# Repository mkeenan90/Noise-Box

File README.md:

# Noise-Box
## Summary 
I wanted to create the foundation for a noise machine to fulfill many different purposes around my house. My daughter falls asleep to the sound of lullabies; my wife and I use a fan for noise in our room. I'd like to replicate these noises with my own design.

The desired feature set is too large for the first iteration. These desired features are: bluetooth music streaming, selectable recordings of family members reading bedtime books, a daytime music box (coffee shop noise, meditation tracks, podcast player, etc.), Alexa capable, and whatever else I can think up.

In order to achieve these features, the first design focuses on just playing music from an SD card and a bunch of buttons for user input.

## Design Specification
### Software
Eagle CAD

##Schematic

##Layout

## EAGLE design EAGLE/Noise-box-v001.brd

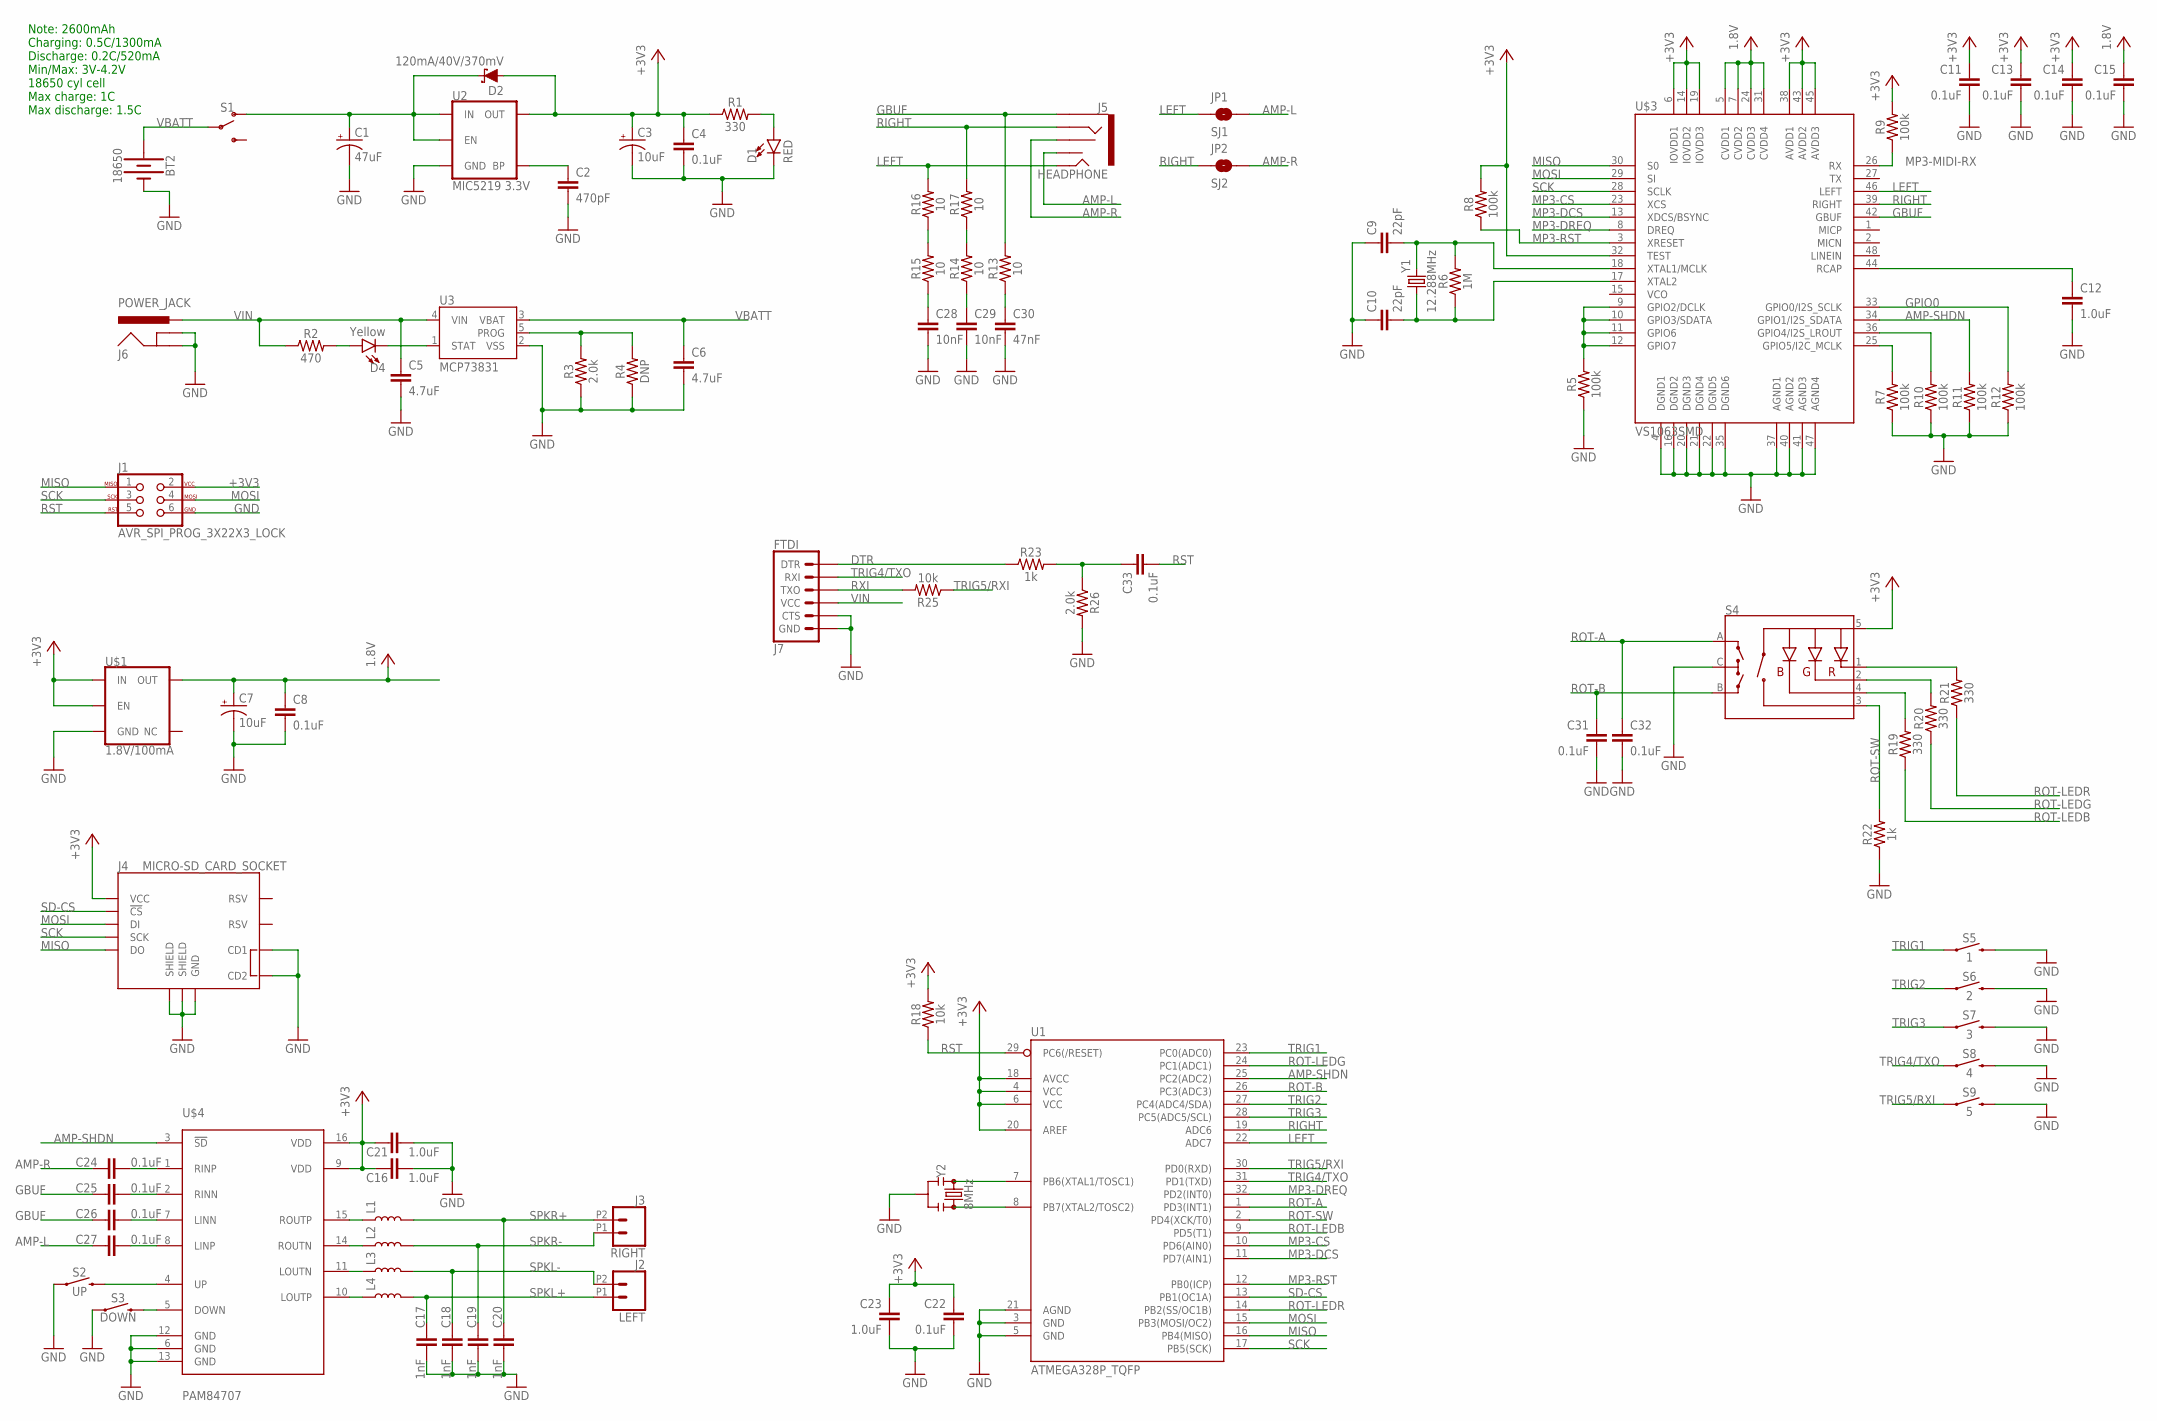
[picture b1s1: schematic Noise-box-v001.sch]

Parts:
BT2: 18650; BATTERY_18650-1043P
C1: 47uF; EIA3528
C2: 470pF; 0603
C3, C7: 10uF; EIA3216
C4, C8, C11, C13, C14, C15, C22, C24, C25, C26, C27, C31, C32, C33: 0.1uF; 0603
C5, C6: 4.7uF; 0603
C9, C10: 22pF; 0603
C12, C16, C21, C23: 1.0uF; 0603
C17, C18, C19, C20: 1nF; 0603
C28, C29: 10nF; 0603
C30: 47nF; 0603
D1: RED; LED-0603
D2: 120mA/40V/370mV; SOD-523
D4: Yellow; LED-0603
J1: AVR_SPI_PROG_3X22X3_LOCK; 2X3_LOCK
J2: LEFT; 1X02_2.54_SCREWTERM
J3: RIGHT; 1X02_2.54_SCREWTERM
J4: MICRO-SD_CARD_SOCKET; MICRO-SD-SOCKET
J5: HEADPHONE; AUDIO-JACK-3.5MM-SMD
J6: POWER_JACK; POWER_JACK_PTH
J7: FTDI; 6_PIN_SERIAL_TARGET_SIDE_W_SILK
JP1: SJ1; SMT-JUMPER_2_NO_SILK
JP2: SJ2; SMT-JUMPER_2_NO_SILK
L1, L2, L3, L4: INDUCTOR-0805-3.3UH; 0805
R1, R19, R20, R21: 330; 0603
R2: 470; 0603
R3, R26: 2.0k; 0603
R4: DNP; 0603
R5, R7, R8, R9, R10, R11, R12: 100k; 0603
R6: 1M; 0603
R13, R14, R15, R16, R17: 10; 0603
R18, R25: 10k; 0603
R22, R23: 1k; 0603
S1: SWITCH-SPDT-SMD-RIGHT-ANGLE; SWITCH_SPST_SMD_A
S2: UP; TACTILE_SWITCH_SMD_4.5MM
S3: DOWN; TACTILE_SWITCH_SMD_4.5MM
S4: ENCODER-RGB-SWITCH; ENCODER_LED_3
S5: 1; TACTILE_SWITCH_SMD_4.5MM
S6: 2; TACTILE_SWITCH_SMD_4.5MM
S7: 3; TACTILE_SWITCH_SMD_4.5MM
S8: 4; TACTILE_SWITCH_SMD_4.5MM
S9: 5; TACTILE_SWITCH_SMD_4.5MM
U1: ATMEGA328P_TQFP; TQFP32-08
U2: MIC5219 3.3V; SOT23-5
U3: MCP73831; SOT23-5
U$1: 1.8V/100mA; SC70
U$3: VS1063SMD; LQFP-48
U$4: PAM84707; SO16
Y1: 12.288MHz; CRYSTAL-SMD-5X3.2-4PAD
Y2: 8MHz; RESONATOR-SMD-3.2X1.3

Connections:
+3V3: C3.+, C4.1, C11.1, C13.1, C14.1, C16.1, C21.1, C22.1, C23.1, D2.A, J1.2, J4.VCC, R1.1, R8.2, R9.2, R18.2, S4.5 (+), U1.4 (VCC), U1.6 (VCC), U1.18 (AVCC), U1.20 (AREF), U2.5 (OUT), U$1.1 (IN), U$1.3 (EN), U$3.6 (IOVDD1), U$3.14 (IOVDD2), U$3.19 (IOVDD3), U$3.32 (TEST), U$3.38 (AVDD1), U$3.43 (AVDD2), U$3.45 (AVDD3), U$4.9 (VDD), U$4.16 (VDD)
AMP-L: C27.1, J5.TSH, JP1.2
AMP-R: C24.1, J5.RSH, JP2.2
AMP-SHDN: R11.2, U1.25 (PC2(ADC2)), U$3.34 (GPIO1/I2S_SDATA), U$4.3 (!SD)
DTR: J7.P$1 (DTR), R23.1
GBUF: C25.1, C26.1, J5.SLEEVE, R13.2, U$3.42 (GBUF)
GND: BT2.GND@1 (-), C1.C (-), C2.2, C3.-, C4.2, C5.2, C6.2, C7.-, C8.2, C9.1, C10.1, C11.2, C12.2, C13.2, C14.2, C15.2, C16.2, C17.2, C18.2, C19.2, C20.2, C21.2, C22.2, C23.2, C28.2, C29.2, C30.2, C31.2, C32.2, D1.C, J1.6, J4.CD1, J4.CD2, J4.GND, J4.GND1 (SHIELD), J4.GND3 (SHIELD), J6.GND, J6.GNDBREAK, J7.P$5 (CTS), J7.P$6 (GND), R3.1, R4.1, R5.1, R7.1, R10.1, R11.1, R12.1, R22.1, R26.2, S2.2 (1), S2.3 (1), S3.2 (1), S3.3 (1), S4.C, S5.1 (2), S5.4 (2), S6.1 (2), S6.4 (2), S7.1 (2), S7.4 (2), S8.1 (2), S8.4 (2), S9.1 (2), S9.4 (2), U1.3 (GND), U1.5 (GND), U1.21 (AGND), U2.2 (GND), U3.2 (VSS), U$1.2 (GND), U$3.4 (DGND1), U$3.16 (DGND2), U$3.20 (DGND3), U$3.21 (DGND4), U$3.22 (DGND5), U$3.35 (DGND6), U$3.37 (AGND1), U$3.40 (AGND2), U$3.41 (AGND3), U$3.47 (AGND4), U$4.6 (GND), U$4.12 (GND), U$4.13 (GND), Y2.2
GPIO0: R12.2, U$3.33 (GPIO0/I2S_SCLK)
LEFT: J5.TIP, JP1.1, R16.2, U1.22 (ADC7), U$3.46 (LEFT)
MISO: J1.1, J4.DO, U1.16 (PB4(MISO)), U$3.30 (S0)
MOSI: J1.4, J4.DI, U1.15 (PB3(MOSI/OC2)), U$3.29 (SI)
MP3-CS: U1.10 (PD6(AIN0)), U$3.23 (XCS)
MP3-DCS: U1.11 (PD7(AIN1)), U$3.13 (XDCS/BSYNC)
MP3-DREQ: U1.32 (PD2(INT0)), U$3.8 (DREQ)
MP3-MIDI-RX: R9.1, U$3.26 (RX)
MP3-RST: R8.1, U1.12 (PB0(ICP)), U$3.3 (XRESET)
unnamed: D4.A, R2.2
unnamed: C2.1, U2.4 (BP)
unnamed: D1.A, R1.2
unnamed: R3.2, R4.2, U3.5 (PROG)
unnamed: U1.7 (PB6(XTAL1/TOSC1)), Y2.1
unnamed: R5.2, U$3.9 (GPIO2/DCLK), U$3.10 (GPIO3/SDATA), U$3.11 (GPIO6), U$3.12 (GPIO7)
unnamed: D4.C, U3.1 (STAT)
unnamed: U1.8 (PB7(XTAL2/TOSC2)), Y2.3
unnamed: L1.1, U$4.15 (ROUTP)
unnamed: L2.1, U$4.14 (ROUTN)
unnamed: L3.1, U$4.11 (LOUTN)
unnamed: L4.1, U$4.10 (LOUTP)
unnamed: C28.1, R15.1
unnamed: R7.2, U$3.25 (GPIO5/I2C_MCLK)
unnamed: R10.2, U$3.36 (GPIO4/I2S_LROUT)
unnamed: C29.1, R14.1
unnamed: C9.2, R6.2, U$3.18 (XTAL1/MCLK), Y1.3 (2)
unnamed: C10.2, R6.1, U$3.17 (XTAL2), Y1.1
unnamed: C30.1, R13.1
unnamed: R15.2, R16.1
unnamed: C12.1, U$3.44 (RCAP)
unnamed: R14.2, R17.1
unnamed: C24.2, U$4.1 (RINP)
unnamed: C33.1, R23.2, R26.1
unnamed: R19.2, S4.4 (-B)
unnamed: R20.2, S4.2 (-G)
unnamed: R21.2, S4.1 (-R)
unnamed: C25.2, U$4.2 (RINN)
unnamed: C26.2, U$4.7 (LINN)
unnamed: C27.2, U$4.8 (LINP)
unnamed: S3.1 (2), S3.4 (2), U$4.5 (DOWN)
unnamed: S2.1 (2), S2.4 (2), U$4.4 (UP)
unnamed: C1.A (+), D2.C, S1.1 (O), U2.1 (IN), U2.3 (EN)
RIGHT: J5.RING, JP2.1, R17.2, U1.19 (ADC6), U$3.39 (RIGHT)
ROT-A: C32.1, S4.A, U1.1 (PD3(INT1))
ROT-B: C31.1, S4.B, U1.26 (PC3(ADC3))
ROT-LEDB: R19.1, U1.9 (PD5(T1))
ROT-LEDG: R20.1, U1.24 (PC1(ADC1))
ROT-LEDR: R21.1, U1.14 (PB2(SS/OC1B))
ROT-SW: R22.2, S4.3 (SW), U1.2 (PD4(XCK/T0))
RST: C33.2, J1.5, R18.1, U1.29 (PC6(/RESET))
RXI: J7.P$2 (TXO), R25.2
SCK: J1.3, J4.SCLK (SCK), U1.17 (PB5(SCK)), U$3.28 (SCLK)
SD-CS: J4.CS (!CS), U1.13 (PB1(OC1A))
SPKL+: C17.1, J2.P1 (1), L4.2
SPKL-: C18.1, J2.P2 (2), L3.2
SPKR+: C20.1, J3.P2 (2), L1.2
SPKR-: C19.1, J3.P1 (1), L2.2
TRIG1: S5.2 (1), S5.3 (1), U1.23 (PC0(ADC0))
TRIG2: S6.2 (1), S6.3 (1), U1.27 (PC4(ADC4/SDA))
TRIG3: S7.2 (1), S7.3 (1), U1.28 (PC5(ADC5/SCL))
TRIG4/TXO: J7.P$3 (RXI), S8.2 (1), S8.3 (1), U1.31 (PD1(TXD))
TRIG5/RXI: R25.1, S9.2 (1), S9.3 (1), U1.30 (PD0(RXD))
VBATT: BT2.PWR@1 (+), C6.1, S1.2, U3.3 (VBAT)
VCC: C7.+, C8.1, C15.1, U$1.5 (OUT), U$3.5 (CVDD1), U$3.7 (CVDD2), U$3.24 (CVDD3), U$3.31 (CVDD4)
VIN: C5.1, J6.PWR, J7.P$4 (VCC), R2.1, U3.4 (VIN)

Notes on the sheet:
Note: 2600mAh Charging: 0.5C/1300mA Discharge: 0.2C/520mA Min/Max: 3V-4.2V 18650 cyl cell Max charge: 1C Max discharge: 1.5C

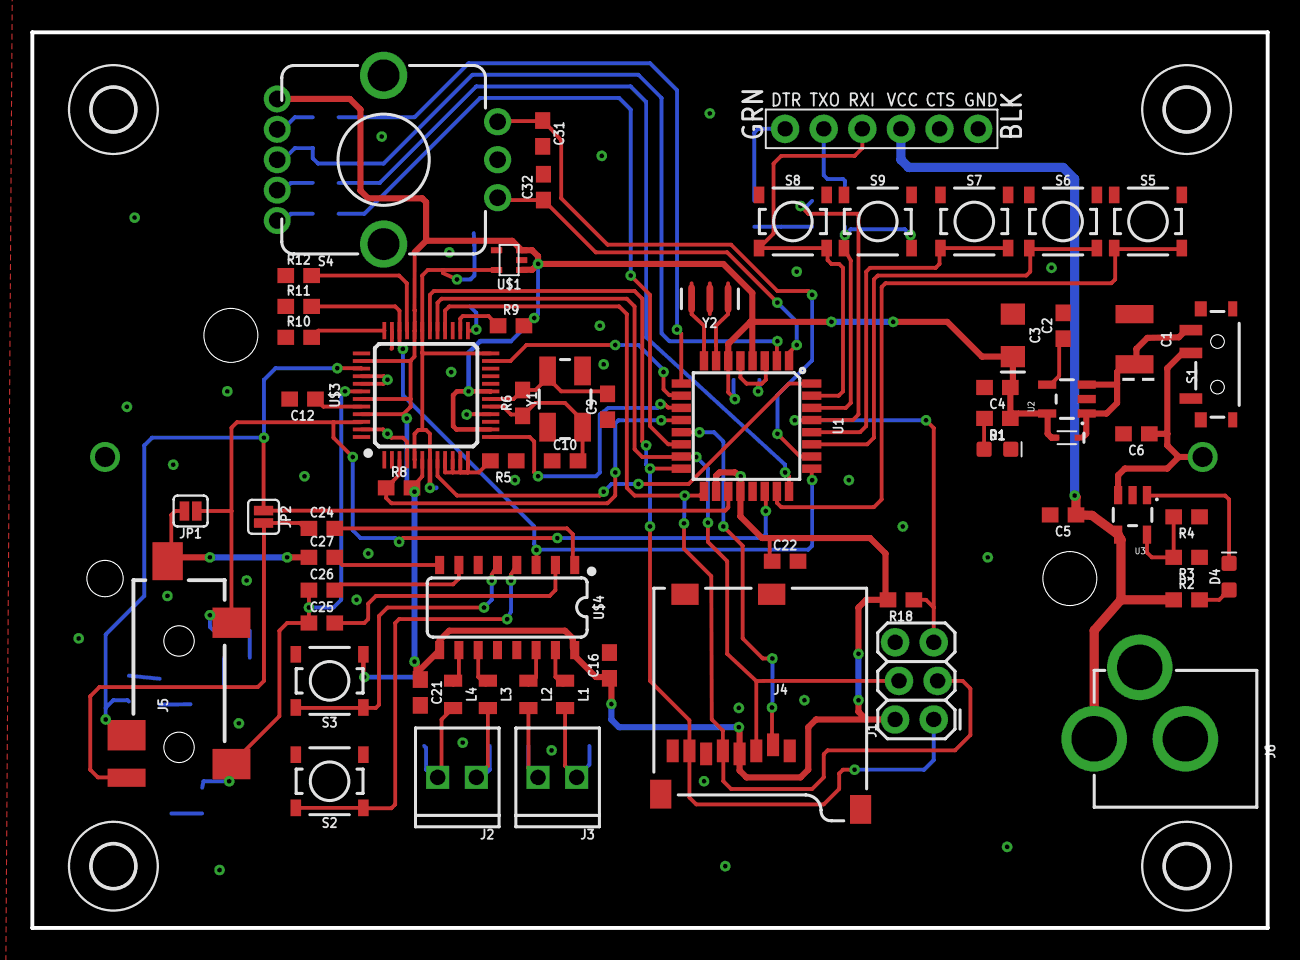
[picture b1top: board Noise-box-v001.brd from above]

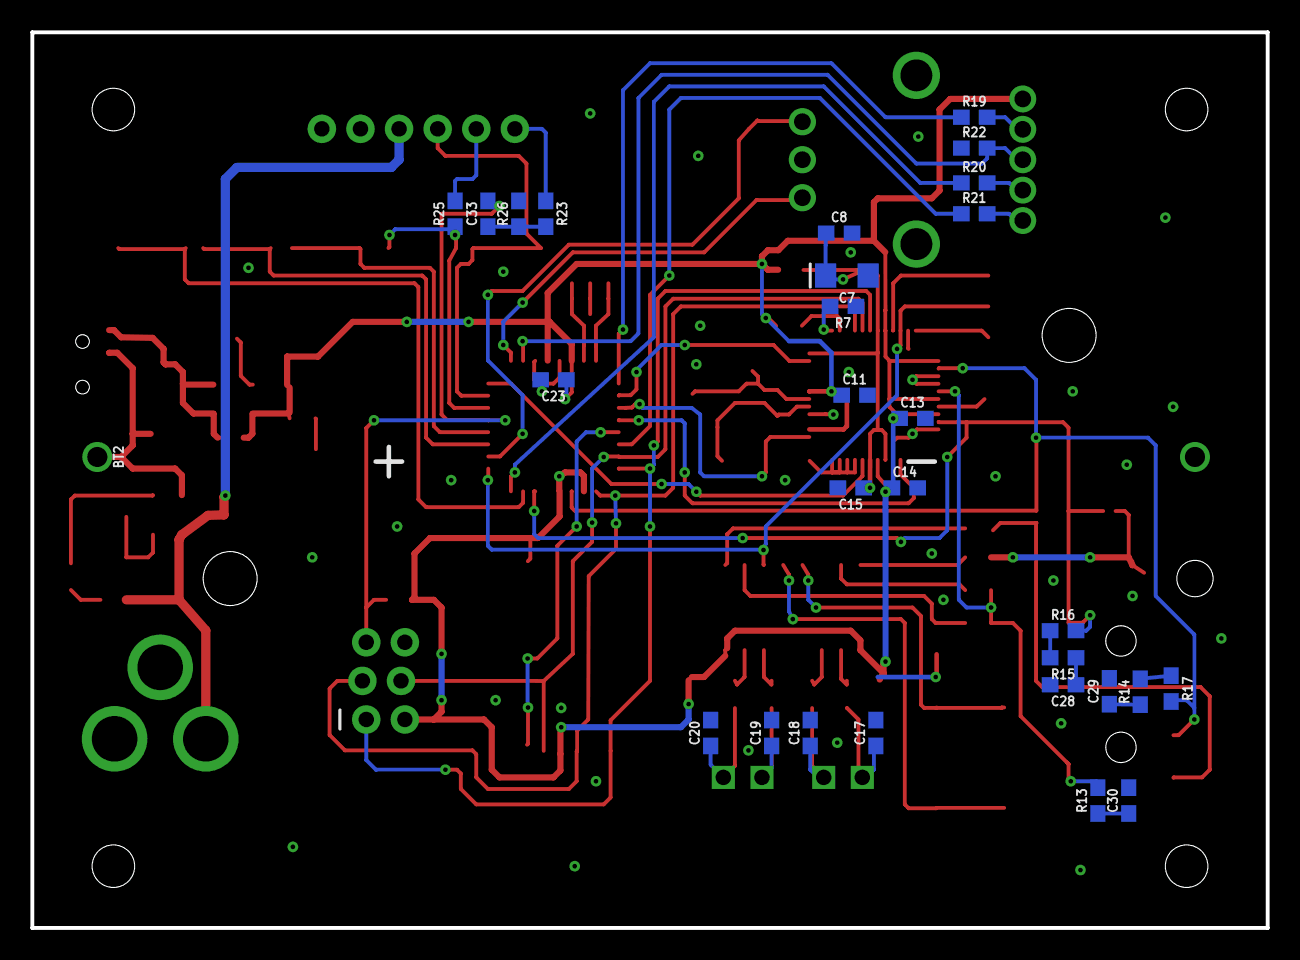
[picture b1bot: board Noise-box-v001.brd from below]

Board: 2 copper layers, 81.3 x 58.9 mm, 96 parts (29 on the bottom side), 72 nets.

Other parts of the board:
U$2, U$5, U$6, U$7: 2,8

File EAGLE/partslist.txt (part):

Partlist

Exported from Noise-box-v001.brd at 3/4/2017 12:36:09 AM

EAGLE Version 6.6.0 Copyright (c) 1988-2014 CadSoft

Assembly variant: 

Part     Value                    Package                         Library                     Position (mm)         Orientation

BT2      18650                    BATTERY_18650-1043P             MAK                         (38.1 27.94)          MR0
C1       47uF                     EIA3528                         SparkFun-Capacitors         (69.723 35.687)       R270
C2       470pF                    0603                            SparkFun-Capacitors         (65.024 36.576)       R90
C3       10uF                     EIA3216                         SparkFun-Capacitors         (61.722 35.941)       R270
C4       0.1uF                    0603                            SparkFun-Capacitors         (60.706 32.512)       R180
C5       4.7uF                    0603                            SparkFun-Capacitors         (65.024 24.13)        R180
C6       4.7uF                    0603                            SparkFun-Capacitors         (69.85 29.464)        R180
C7       10uF                     EIA3216                         SparkFun-Capacitors         (24.892 39.878)       MR180
C8       0.1uF                    0603                            SparkFun-Capacitors         (25.4 42.672)         MR0
C9       22pF                     0603                            SparkFun-Capacitors         (35.052 31.242)       R90
C10      22pF                     0603                            SparkFun-Capacitors         (32.258 27.686)       R0
C11      0.1uF                    0603                            SparkFun-Capacitors         (24.384 32.004)       MR0
C12      1.0uF                    0603                            SparkFun-Capacitors         (14.986 31.75)        R180
C13      0.1uF                    0603                            SparkFun-Capacitors         (20.574 30.48)        MR0
C14      0.1uF                    0603                            SparkFun-Capacitors         (21.082 25.908)       MR0
C15      0.1uF                    0603                            SparkFun-Capacitors         (24.638 25.908)       MR180
C16      1.0uF                    0603                            SparkFun-Capacitors         (35.179 14.224)       R90
C17      1nF                      0603                            SparkFun-Capacitors         (22.987 9.779)        MR90
C18      1nF                      0603                            SparkFun-Capacitors         (27.305 9.779)        MR90
C19      1nF                      0603                            SparkFun-Capacitors         (29.845 9.779)        MR90
C20      1nF                      0603                            SparkFun-Capacitors         (33.8582 9.779)       MR90
C21      1.0uF                    0603                            SparkFun-Capacitors         (22.733 12.446)       R270
C22      0.1uF                    0603                            SparkFun-Capacitors         (46.736 21.082)       R0
C23      1.0uF                    0603                            SparkFun-Capacitors         (44.196 33.02)        MR180
C24      0.1uF                    0603                            SparkFun-Capacitors         (16.256 23.241)       R0
C25      0.1uF                    0603                            SparkFun-Capacitors         (16.256 17.018)       R0
C26      0.1uF                    0603                            SparkFun-Capacitors         (16.256 19.177)       R0
C27      0.1uF                    0603                            SparkFun-Capacitors         (16.256 21.336)       R0
C28      10nF                     0603                            SparkFun-Capacitors         (10.668 12.954)       MR180
C29      10nF                     0603                            SparkFun-Capacitors         (7.62 12.5222)        MR90
C30      47nF                     0603                            SparkFun-Capacitors         (6.35 5.334)          MR90
C31      0.1uF                    0603                            SparkFun-Capacitors         (30.7848 49.2252)     R270
C32      0.1uF                    0603                            SparkFun-Capacitors         (30.8356 45.6946)     R90
C33      0.1uF                    0603                            SparkFun-Capacitors         (48.514 43.942)       MR90
D1       RED                      LED-0603                        SparkFun-LED                (60.706 28.448)       R0
D2       120mA/40V/370mV          SOD-523                         SparkFun-DiscreteSemi       (65.278 29.21)        R0
D4       Yellow                   LED-0603                        SparkFun-LED                (75.946 20.066)       R90
J1       AVR_SPI_PROG_3X22X3_LOCK 2X3_LOCK                        SparkFun-Connectors         (56.642 10.668)       R90
J2       LEFT                     1X02_2.54_SCREWTERM             SparkFun-Connectors         (26.416 6.858)        R180
J3       RIGHT                    1X02_2.54_SCREWTERM             SparkFun-Connectors         (33.02 6.858)         R180
J4       MICRO-SD_CARD_SOCKET     MICRO-SD-SOCKET                 SparkFun-Connectors         (38.1 19.304)         R180
J5       HEADPHONE                AUDIO-JACK-3.5MM-SMD            SparkFun-Connectors         (6.858 5.334)         R90
J6       POWER_JACK               POWER_JACK_PTH                  SparkFun-Connectors         (80.772 9.398)        R90
J7       FTDI                     6_PIN_SERIAL_TARGET_SIDE_W_SILK SparkFun-Connectors         (53.086 49.53)        R0
JP1      SJ1                      SMT-JUMPER_2_NO_SILK            SparkFun-Jumpers            (7.62 24.384)         R180
JP2      SJ2                      SMT-JUMPER_2_NO_SILK            SparkFun-Jumpers            (12.4206 24.003)      R270
L1                                0805                            SparkFun-Coils              (32.258 12.319)       R270
L2                                0805                            SparkFun-Coils              (29.845 12.319)       R270
L3                                0805                            SparkFun-Coils              (27.178 12.319)       R270
L4                                0805                            SparkFun-Coils              (24.892 12.319)       R270
R1       330                      0603                            SparkFun-Resistors          (60.706 30.48)        R180
R2       470                      0603                            SparkFun-Resistors          (73.152 18.542)       R0
R3       2.0k                     0603                            SparkFun-Resistors          (73.152 21.336)       R180
R4       DNP                      0603                            SparkFun-Resistors          (73.152 24.003)       R180
R5       100k                     0603                            SparkFun-Resistors          (28.194 27.686)       R180
R6       1M                       0603                            SparkFun-Resistors          (29.464 31.496)       R90
R7       100k                     0603                            SparkFun-Resistors          (25.146 37.846)       MR180
R8       100k                     0603                            SparkFun-Resistors          (21.336 25.908)       R0
R9       100k                     0603                            SparkFun-Resistors          (28.702 36.576)       R0
R10      100k                     0603                            SparkFun-Resistors          (14.732 35.814)       R0
R11      100k                     0603                            SparkFun-Resistors          (14.732 37.846)       R0
R12      100k                     0603                            SparkFun-Resistors          (14.732 39.878)       R0
R13      10                       0603                            SparkFun-Resistors          (8.382 5.334)         MR90
R14      10                       0603                            SparkFun-Resistors          (5.588 12.4968)       MR90
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
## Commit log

2017-02-08 :lollipop: Added .gitattributes & .gitignore files
2017-02-08 Project Setup
    Started project files. Included outline, sch, brd, pdf's for part
    research
2017-02-10 Sch update - power
    Added voltage regulators and supporting components.
2017-02-16 Schematic work
    Added regulator, battery charging circuit
2017-02-16 Low voltage rail
    Added 1.8V rail to accomodate codec IC core
2017-02-16 micro sd
    Added micro sd socket, to hold music tracks
2017-02-17 mp3 decoder
    Added VL1063 codec, headphone jack
2017-02-17 clk
    Added crystal for vs1063
2017-02-17 vs1063
    Added all support circuitry to vs1063, including extra locations for cap
    filtering
2017-02-17 Audio amp
    Added simple audio amplifier
2017-02-20 Battery
    Picked battery with best available Wh/dollar
2017-02-20 Capacitor sizes
    research linear regulator capacitor sizing
2017-02-21 Layout
    First pass at layout. Established rough board dimensions. It seems that
    establishing GND different than Battery (-) will necessitate a long
    trace through the middle of the board. This might be avoided by going
    with a wire lead version of the battery holder and avoiding that
    unwanted trace by use of wires.
2017-02-21 Pictures
    Added layout pic
2017-02-21 img
    Changed picture dir to "img". Added schematic image
2017-02-24 Layout updates
    Adjusted battery holder package. Began layout, establishing rough
    dimensions of the board.
2017-02-25 Layout
    continued layout design. updated a few minor schematic errors
2017-02-25 Triggers
    Added momentary buttons to act as triggers. These will choose between
    music categories, songs, or other user input features.
2017-03-03 More layout, buttons, debug header
    Added a handful of buttons and a rotary switch to handle user inputs
    such a track selection, volume knob, pause/play, etc. Added 5 pin debug
    header for FTDI to USB adapter I have. Advanced the layout - nearly
    complete.
2017-03-03 Updated images
    Added a new image of the layout and schematic
2017-03-03 Image
    Corrected schematic image file type
2017-03-03 Readme update
    Added a bit of formatting. Continued the explanation of the project.
2017-03-03 Layout
    Further layout
2017-03-04 Layout, CAM, BoM, Datasheets
    Finished layout, generated CAM files for manufacturing, generated BoM.
    Added several datasheets for reference

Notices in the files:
parts and their libraries:
SparkFun-IC-Microcontroller: Licensing: Creative Commons ShareAlike 4.0 International - https://creativecommons.org/licenses/by-sa/4.0
